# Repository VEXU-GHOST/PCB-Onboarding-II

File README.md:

# PCB-Onboarding-II
Repo for the second part of PCB onboarding of the VEXU GHOST hardware team

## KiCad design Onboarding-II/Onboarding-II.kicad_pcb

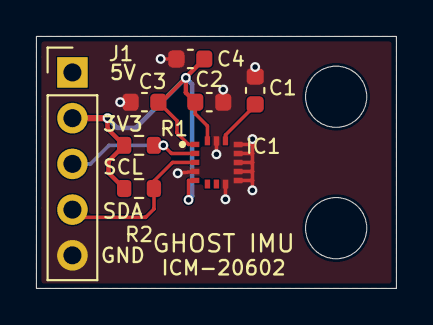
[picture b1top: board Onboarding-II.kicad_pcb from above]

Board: 2 copper layers, 20.0 x 14.0 mm, 10 parts (0 on the bottom side), 5 nets.

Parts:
C1, C2: 100 nF; C_0603_1608Metric
C3: 10 nF; C_0603_1608Metric
C4: 2.2 uF; C_0603_1608Metric
H1, H2: 3.4 mm; MountingHole_3.4mm
IC1: ICM-20602; IAM20680HP
J1: Conn_01x05; PinHeader_1x05_P2.54mm_Vertical
R1, R2: 10 k; R_0603_1608Metric

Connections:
+3.3V: C2.1, C3.1, C4.1, IC1.1, IC1.5, IC1.16, J1.2, R1.1, R2.1
GND: C1.2, C2.2, C3.2, C4.2, IC1.4, IC1.8, IC1.9, IC1.10, IC1.11, IC1.12, IC1.13, IC1.15, J1.5
unnamed: C1.1, IC1.14
SCL: IC1.2, J1.3, R1.2
SDA: IC1.3, J1.4, R2.2

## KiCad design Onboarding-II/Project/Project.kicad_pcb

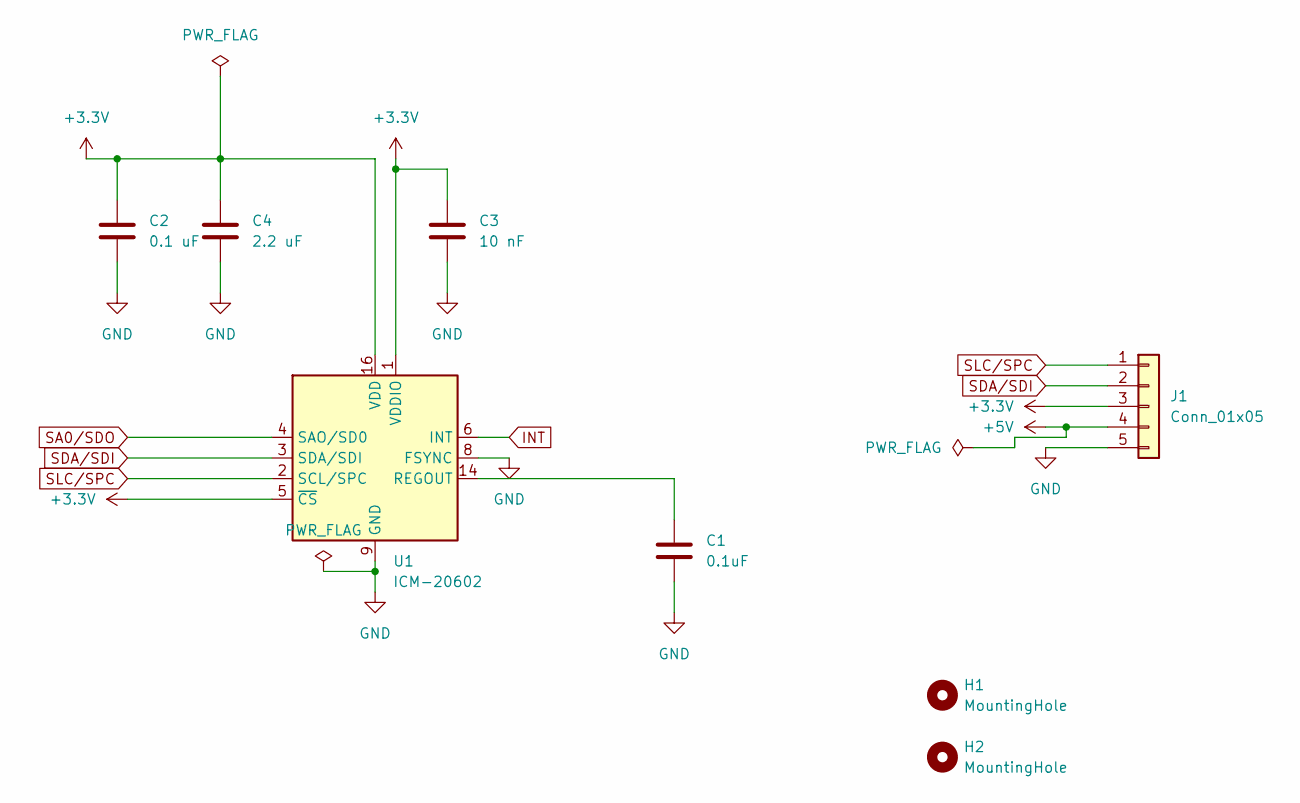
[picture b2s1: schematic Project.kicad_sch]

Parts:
C1: 0.1uF; C_0603_1608Metric
C2: 0.1 uF; C_0603_1608Metric
C3: 10 nF; C_0603_1608Metric
C4: 2.2 uF; C_0603_1608Metric
H1, H2: MountingHole; MountingHole_3.2mm_M3
J1: Conn_01x05; PinHeader_1x05_P2.54mm_Horizontal
U1: ICM-20602; LGA-16_3x3mm_P0.5mm_LayoutBorder3x5y

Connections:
+3.3V: C2.1, C3.1, C4.1, J1.3, U1.1 (VDDIO), U1.5 (~CS), U1.16 (VDD)
+5V: J1.4
GND: C1.2, C2.2, C3.2, C4.2, J1.5, U1.8 (FSYNC), U1.9 (GND), U1.10 (GND), U1.11 (GND), U1.12 (GND), U1.13 (GND), U1.15 (GND)
INT: U1.6 (INT)
unnamed: C1.1, U1.14 (REGOUT)
SA0/SDO: U1.4 (SAO/SD0)
SDA/SDI: J1.2, U1.3 (SDA/SDI)
SLC/SPC: J1.1, U1.2 (SCL/SPC)

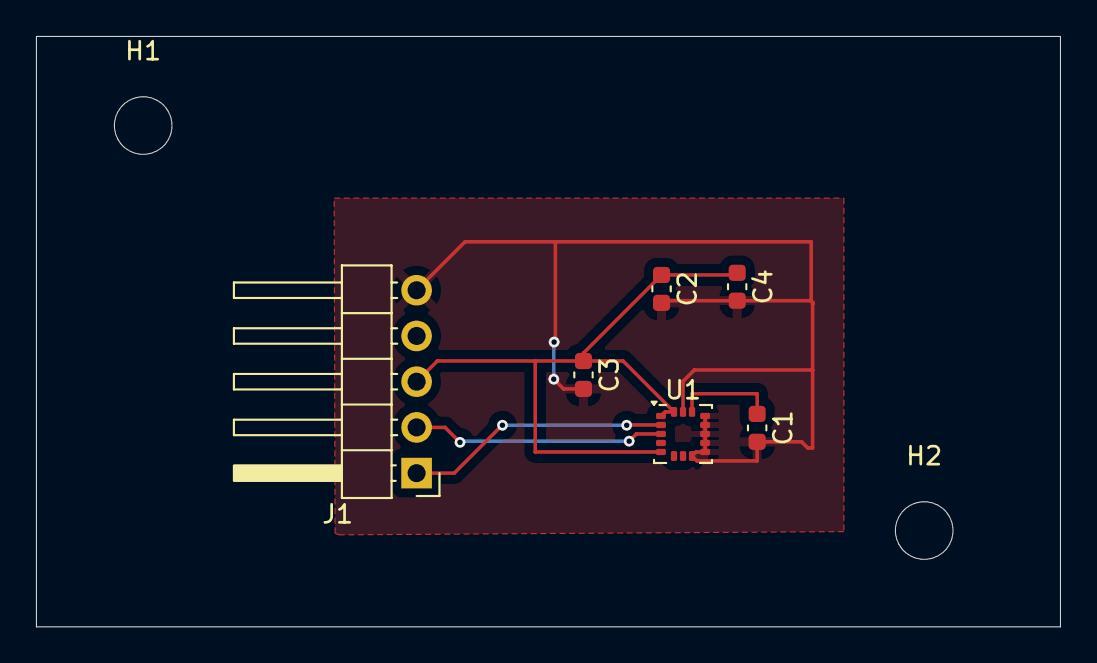
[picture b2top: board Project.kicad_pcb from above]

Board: 2 copper layers, 56.9 x 32.8 mm, 8 parts (0 on the bottom side), 5 nets.
